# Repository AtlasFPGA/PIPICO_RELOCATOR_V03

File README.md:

# PIPICO_RELOCATOR_V0

Group ATLAS in Telegram: https://t.me/INICIATIVAATLAS

Agregadas salidas para poder usar módulos I2S Texas Instruments PCM5102A

Visionado del ajuste de pares diferenciales:

Modificaciones sobre el recolocador PI-PICO que ha realizado Carlos Palmero, con el objetivo de que quede más centrada la placa en la versión de coste reducido de ATLAS, es decir "¡la roja!"
Marcando el uso de un módulo I2S de bajo costo como es el Texas Instruments PCM5102A, y posiblemente en el futuro un micrófono capacitivo I2S.

El proyecto pone a disposición los ficheros necesarios del paquete de desarrollo KICAD.
Se han calculado todas las pistas de los pares diferenciales y en este modelo se han ajustado por completo, desde la medición de la longitud de las pistas en la placa "¡la roja!" para que la distancia de los pares coincidan en todas las pistas.

Vistas en 3D del montaje, se puede ver que he dejado el orificio para ajustar la posición de la placa, y que se ha recortado la zona del bus de 40 pines.

### Vista 1 Tridimensional:

### Vista 2 Tridimensional:

### Vista 3 Tridimensional:

Licencia:
CERN OHL V2 STRICT
https://ohwr.org/cern_ohl_s_v2.txt

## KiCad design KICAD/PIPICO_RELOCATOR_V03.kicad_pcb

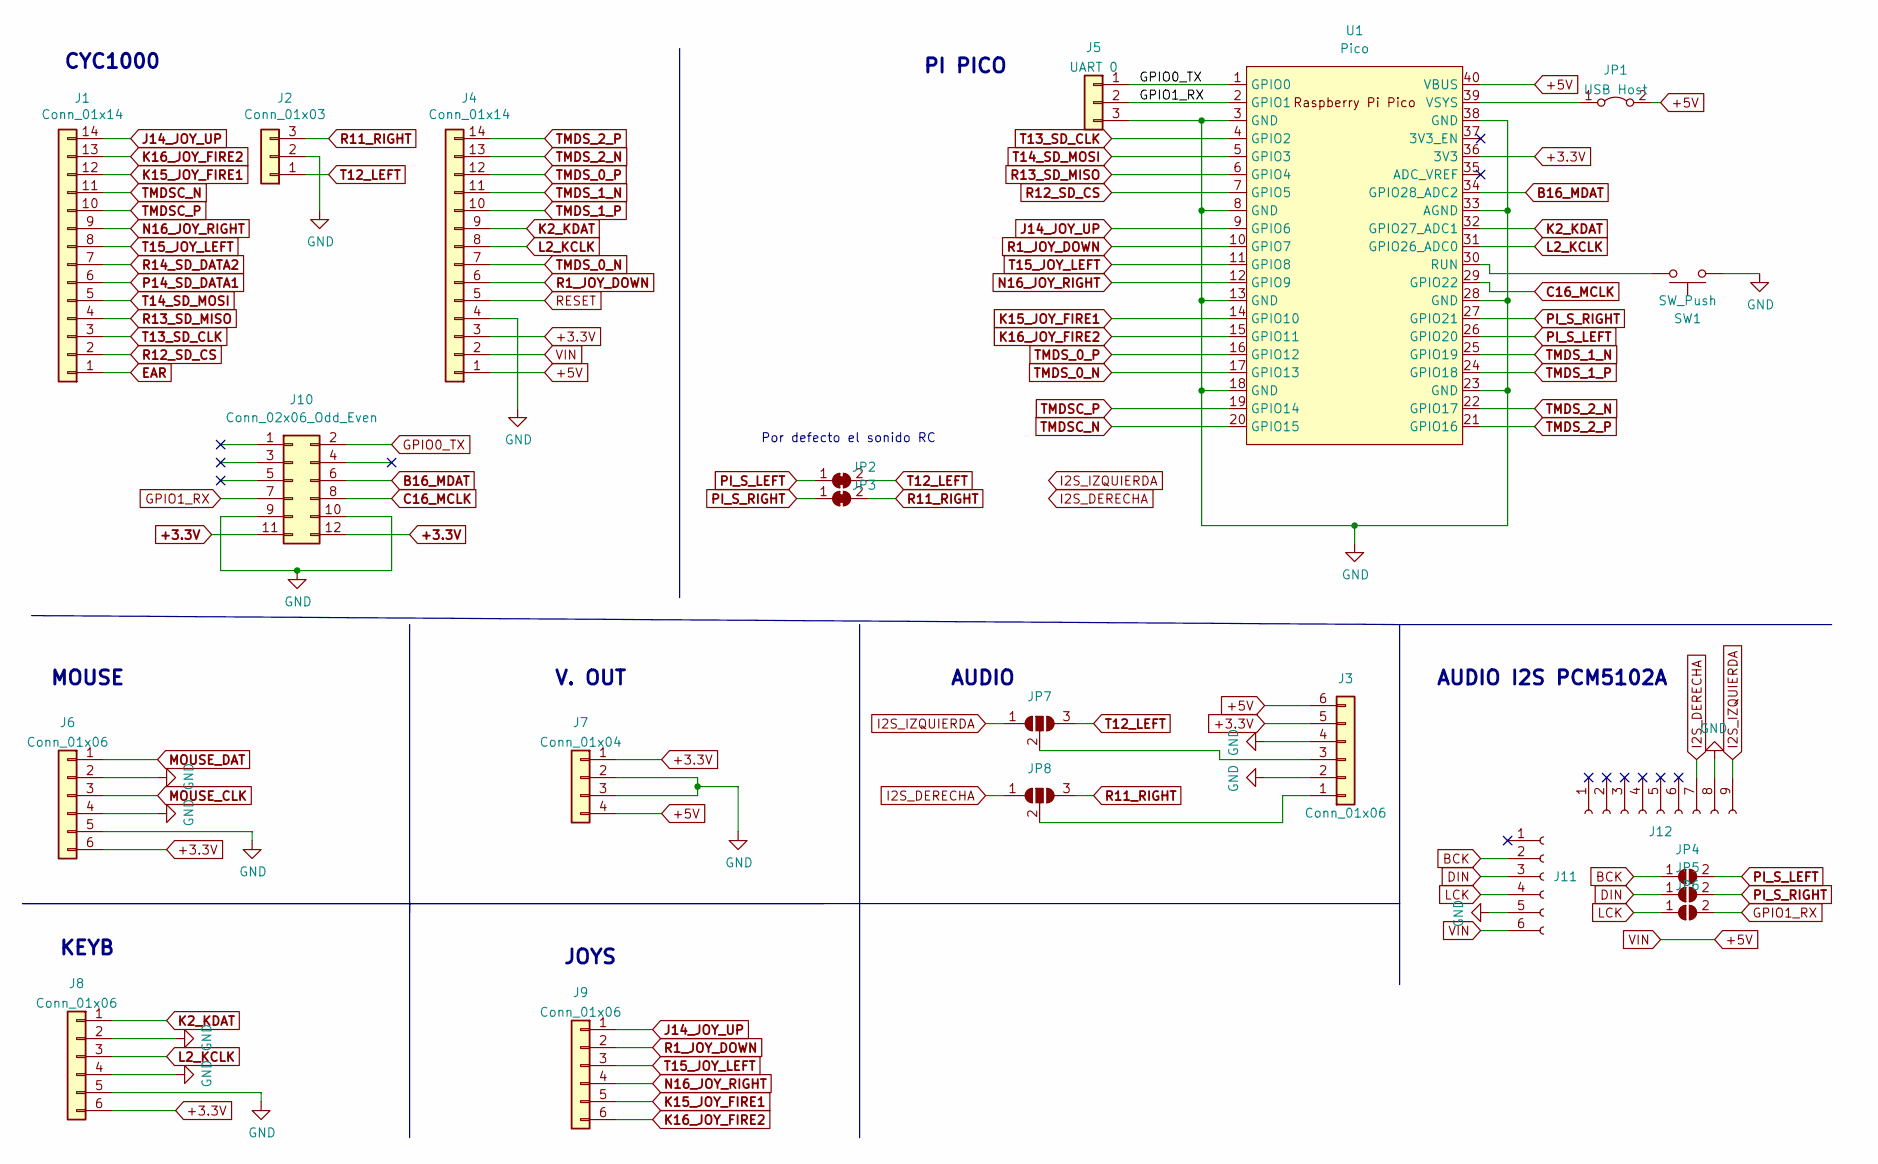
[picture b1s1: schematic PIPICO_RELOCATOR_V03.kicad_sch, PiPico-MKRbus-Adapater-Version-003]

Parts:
J1, J4: Conn_01x14; PinHeader_1x14_P2.54mm_Vertical
J2: Conn_01x03; PinHeader_1x03_P2.54mm_Vertical
J3, J6, J8, J9: Conn_01x06; PinHeader_1x06_P2.54mm_Vertical
J5: UART 0; PinHeader_1x03_P2.54mm_Vertical
J7: Conn_01x04; PinHeader_1x04_P2.54mm_Vertical
J10: Conn_02x06_Odd_Even; PinHeader_2x06_P2.54mm_Vertical
J11: Conn_01x06_Female; PinSocket_1x06_P2.54mm_Vertical
J12: Conn_01x09_Female; PinSocket_1x09_P2.54mm_Vertical
JP1: USB Host; PinHeader_1x02_P2.54mm_Vertical
JP2, JP3: SolderJumper_2_Bridged; SolderJumper-2_P1.3mm_Bridged2Bar_RoundedPad1.0x1.5mm
JP4, JP5, JP6: SolderJumper_2_Open; SolderJumper-2_P1.3mm_Open_RoundedPad1.0x1.5mm
JP7, JP8: SolderJumper_3_Open; SolderJumper-3_P1.3mm_Open_RoundedPad1.0x1.5mm
SW1: SW_Push; SW_PUSH_6mm
U1: Pico; RPi_Pico_SMD_TH

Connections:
+3.3V: J3.5, J4.3, J6.6, J7.1, J8.6, J10.11, J10.12, U1.36 (3V3)
+5V: J3.6, J4.1, J4.2, J7.4, J11.6, JP1.2 (B), U1.40 (VBUS)
B16_MDAT: J10.6, U1.34 (GPIO28_ADC2)
BCK: J11.2, JP4.1 (A)
C16_MCLK: J10.8, U1.29 (GPIO22)
DIN: J11.3, JP5.1 (A)
EAR: J1.1
GND: J2.2, J3.2, J3.4, J4.4, J5.3, J6.2, J6.4, J6.5, J7.2, J7.3, J8.2, J8.4, J8.5, J10.9, J10.10, J11.5, J12.8, SW1.2, U1.3 (GND), U1.8 (GND), U1.13 (GND), U1.18 (GND), U1.23 (GND), U1.28 (GND), U1.33 (AGND), U1.38 (GND)
GPIO0_TX: J5.1, J10.2, U1.1 (GPIO0)
GPIO1_RX: J5.2, J10.7, JP6.2 (B), U1.2 (GPIO1)
I2S_DERECHA: J12.7, JP8.1 (A)
I2S_IZQUIERDA: J12.9, JP7.1 (A)
J14_JOY_UP: J1.14, J9.1, U1.9 (GPIO6)
K2_KDAT: J4.9, J8.1, U1.32 (GPIO27_ADC1)
K15_JOY_FIRE1: J1.12, J9.5, U1.14 (GPIO10)
K16_JOY_FIRE2: J1.13, J9.6, U1.15 (GPIO11)
L2_KCLK: J4.8, J8.3, U1.31 (GPIO26_ADC0)
LCK: J11.4, JP6.1 (A)
MOUSE_CLK: J6.3
MOUSE_DAT: J6.1
N16_JOY_RIGHT: J1.9, J9.4, U1.12 (GPIO9)
unnamed: J3.1, JP8.2 (C)
unnamed: J3.3, JP7.2 (C)
unnamed: JP1.1 (A), U1.39 (VSYS)
unnamed: SW1.1, U1.30 (RUN)
P14_SD_DATA1: J1.6
PI_S_LEFT: JP2.1 (A), JP4.2 (B), U1.26 (GPIO20)
PI_S_RIGHT: JP3.1 (A), JP5.2 (B), U1.27 (GPIO21)
R1_JOY_DOWN: J4.6, J9.2, U1.10 (GPIO7)
R11_RIGHT: J2.3, JP3.2 (B), JP8.3 (B)
R12_SD_CS: J1.2, U1.7 (GPIO5)
R13_SD_MISO: J1.4, U1.6 (GPIO4)
R14_SD_DATA2: J1.7
RESET: J4.5
T12_LEFT: J2.1, JP2.2 (B), JP7.3 (B)
T13_SD_CLK: J1.3, U1.4 (GPIO2)
T14_SD_MOSI: J1.5, U1.5 (GPIO3)
T15_JOY_LEFT: J1.8, J9.3, U1.11 (GPIO8)
TMDSC_N: J1.11, U1.20 (GPIO15)
TMDSC_P: J1.10, U1.19 (GPIO14)
TMDS_0_N: J4.7, U1.17 (GPIO13)
TMDS_0_P: J4.12, U1.16 (GPIO12)
TMDS_1_N: J4.11, U1.25 (GPIO19)
TMDS_1_P: J4.10, U1.24 (GPIO18)
TMDS_2_N: J4.13, U1.22 (GPIO17)
TMDS_2_P: J4.14, U1.21 (GPIO16)

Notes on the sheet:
MOUSE
CYC1000
AUDIO
KEYB
JOYS
PI PICO
Por defecto el sonido RC
AUDIO I2S PCM5102A
V. OUT

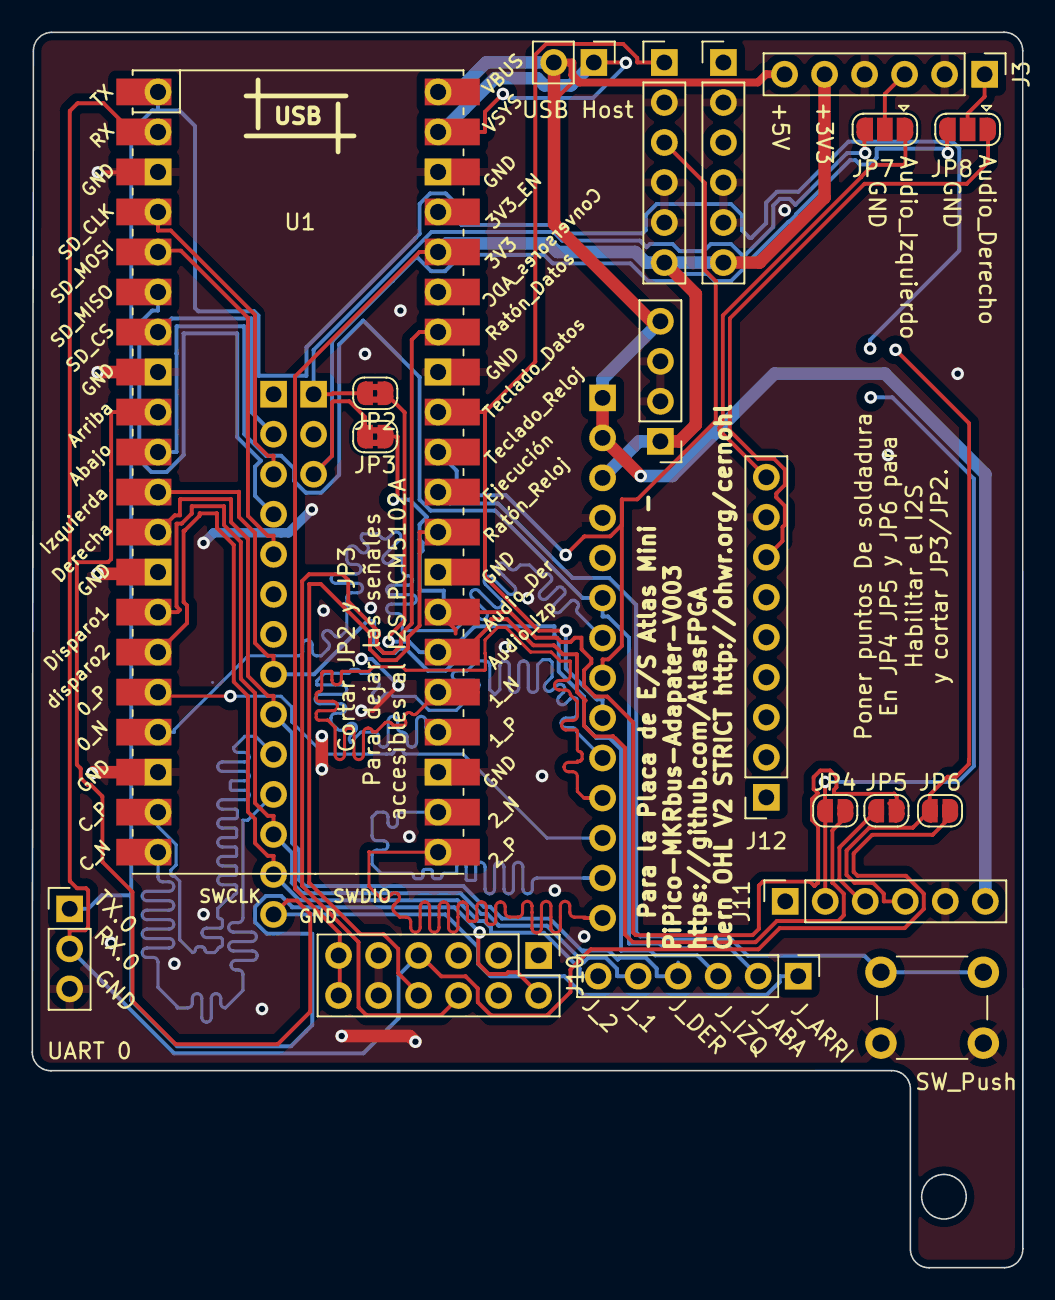
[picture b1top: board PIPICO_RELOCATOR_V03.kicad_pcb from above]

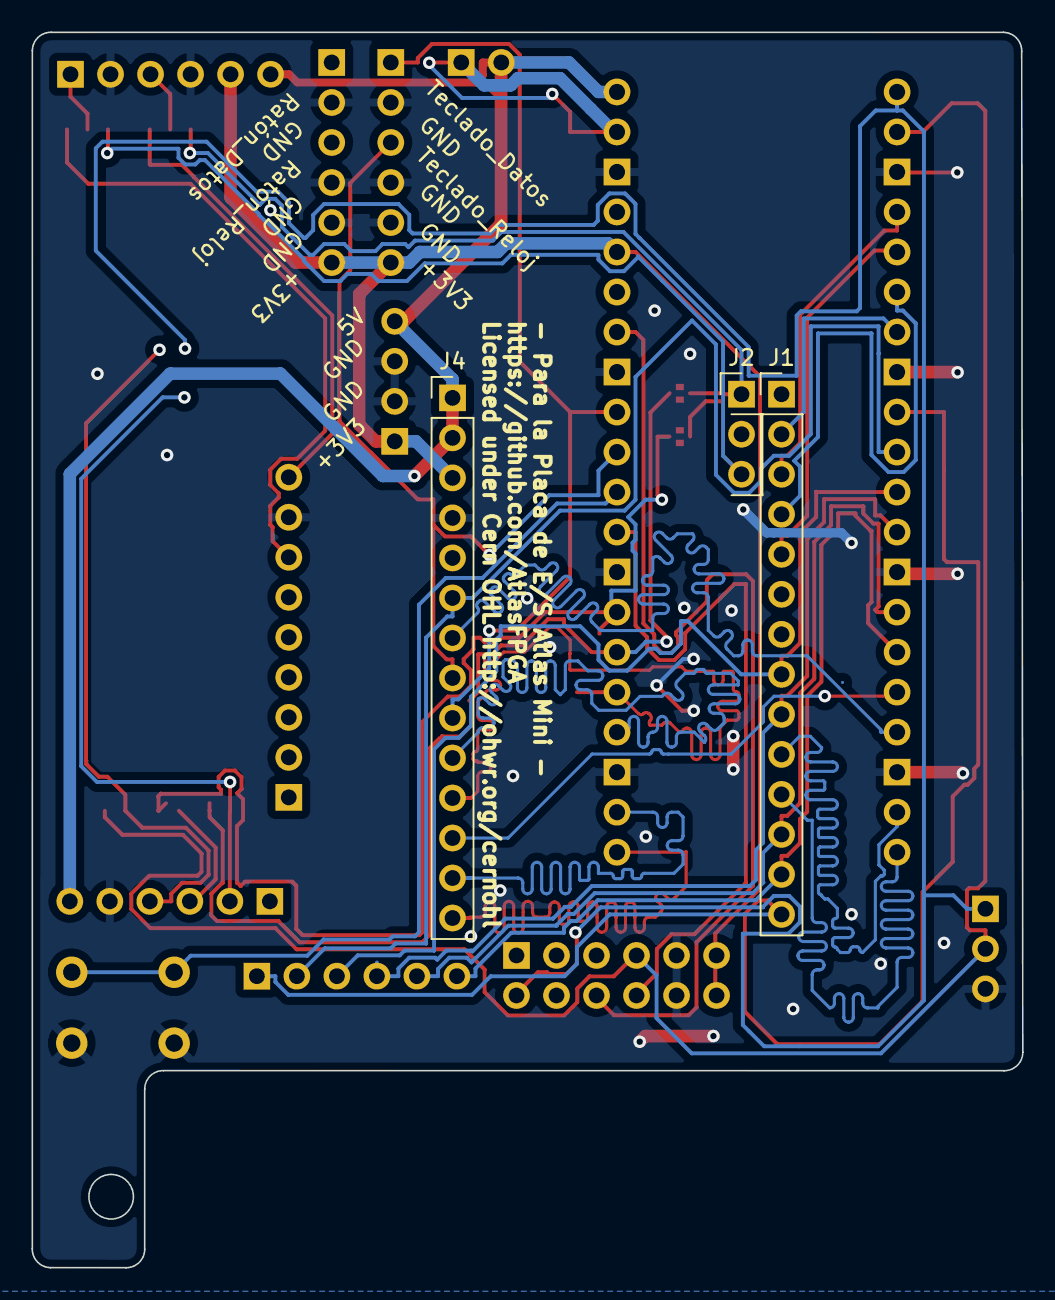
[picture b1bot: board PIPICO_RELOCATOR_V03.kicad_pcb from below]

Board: 2 copper layers, 62.9 x 78.4 mm, 22 parts (3 on the bottom side), 40 nets.

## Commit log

2023-09-21 Primera información sobre la placa V03 de PIPICO README.md
2023-09-21 Pantallazos del recolocador PIPICO con ajuste de lineas de pares diferenciales
2023-09-21 Agregar fotos del desarrollo con i2s para pi-pico README.md
2023-09-21 Correcciones del texto del README.md
2023-09-21 Cambio en los incrustados de imágenes README.md
2023-09-21 Recolocador en su tercera versión ajustado a las dimensiones de la ATLAS MINI
2023-09-21 subir pantallazo de la visión tridimensional donde aparece la SD y el vídeo digital.
2023-09-21 Actualización del README.md incorporando una tercera vista tridimensional.
2023-09-21 Agregar tercera vista tridimensional a README.md
2023-09-21 Agregar el tipo de licencia README.md
2023-12-11 Group ATLAS in Telegram: https://t.me/INICIATIVAATLAS

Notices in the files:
KICAD/PIPICO_RELOCATOR_V03.kicad_pcb:
Licensed under Cern OHL http://ohwr.org/cernohl
Cern OHL V2 STRICT http://ohwr.org/cernohl
